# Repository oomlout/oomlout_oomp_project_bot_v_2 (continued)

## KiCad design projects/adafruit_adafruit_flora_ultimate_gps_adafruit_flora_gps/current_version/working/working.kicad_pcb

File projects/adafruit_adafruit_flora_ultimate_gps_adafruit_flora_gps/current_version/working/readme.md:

# adafruit_flora_ultimate_gps
 
## summary 
* id: adafruit_adafruit_flora_ultimate_gps_adafruit_flora_gps
* user: adafruit
* name: adafruit_flora_ultimate_gps
* board: adafruit_flora_gps
* repo: https://github.com/adafruit/Adafruit-Flora-Ultimate-GPS

* src_file_repo_sch: 
* src_file_repo_sch_link: https://github.com/adafruit/Adafruit-Flora-Ultimate-GPS/tree/master/
* full details link: https://github.com/oomlout/oomlout_oomp_project_bot_v_2/tree/main/projects/adafruit_adafruit_flora_ultimate_gps_adafruit_flora_gps/current_version/working  

## schematic  
  
[schematic (pdf)](working_schematic.pdf) 

## pcb  

[board (pdf)](working.pdf)  

## working_bom
| Id | Designator | Footprint | Quantity | Designation | Supplier and ref |  | None | 
| --- | --- | --- | --- | --- | --- | --- | --- | 
| 1 | FID2,FID1 | FIDUCIAL_1MM | 2 | FIDUCIAL" |  |  | [''] | 
| 2 | C2 | 0805 | 1 | 10uF |  |  | [''] | 
| 3 | TX0,TP4,UNK3V3IN0,GND0,RX0,TP1,GND1 | SEWINGTAP_2.0 | 7 | SEWTAP-2.0IN |  |  | [''] | 
| 4 | U$6 | ADAFRUIT_5MM | 1 |  |  |  | [''] | 
| 5 | R1 | 0805 | 1 | 1K |  |  | [''] | 
| 6 | LED1 | CHIPLED_0805 | 1 | FIX |  |  | [''] | 
| 7 | U1 | FGPMMOPA6H | 1 | FGPMMOPA6H |  |  | [''] | 
| 8 | FB1 | 0805 | 1 | Ferrite |  |  | [''] | 
| 9 | U$20 | U.FL | 1 | U.FL |  |  | [''] | 
| 10 | U$7 | FLORASMALL | 1 |  |  |  | [''] | 

## bom_schematic
| Ref | Qnty | Value | Cmp name | Footprint | Description | Vendor | DNP | 
| --- | --- | --- | --- | --- | --- | --- | --- | 
| C2 | 1 | 10uF | CAP_CERAMIC0805 | working:0805 |  |  |  | 
| FB1 | 1 | Ferrite | FERRITE0805 | working:0805 |  |  |  | 
| FID1, FID2 | 2 | FIDUCIAL"" | FIDUCIAL{dblquote}{dblquote} | working:FIDUCIAL_1MM |  |  |  | 
| GND0, GND1 | 2 | SEWTAP-2.0IN | SEWTAP-2.0IN | working:SEWINGTAP_2.0 |  |  |  | 
| LED1 | 1 | FIX | LED0805 | working:CHIPLED_0805 |  |  |  | 
| R1 | 1 | 1K | RESISTOR0805 | working:0805 |  |  |  | 
| RX0 | 1 | SEWTAP-2.0IN | SEWTAP-2.0IN | working:SEWINGTAP_2.0 |  |  |  | 
| TP1, TP4 | 2 | SEWTAP-2.0IN | SEWTAP-2.0IN | working:SEWINGTAP_2.0 |  |  |  | 
| TX0 | 1 | SEWTAP-2.0IN | SEWTAP-2.0IN | working:SEWINGTAP_2.0 |  |  |  | 
| U1 | 1 | FGPMMOPA6H | GPS_FGPMMOPA6H | working:FGPMMOPA6H |  |  |  | 
| U$20 | 1 | U.FL | U.FL | working:U.FL |  |  |  | 
| UNK3V3IN0 | 1 | SEWTAP-2.0IN | SEWTAP-2.0IN | working:SEWINGTAP_2.0 |  |  |  |

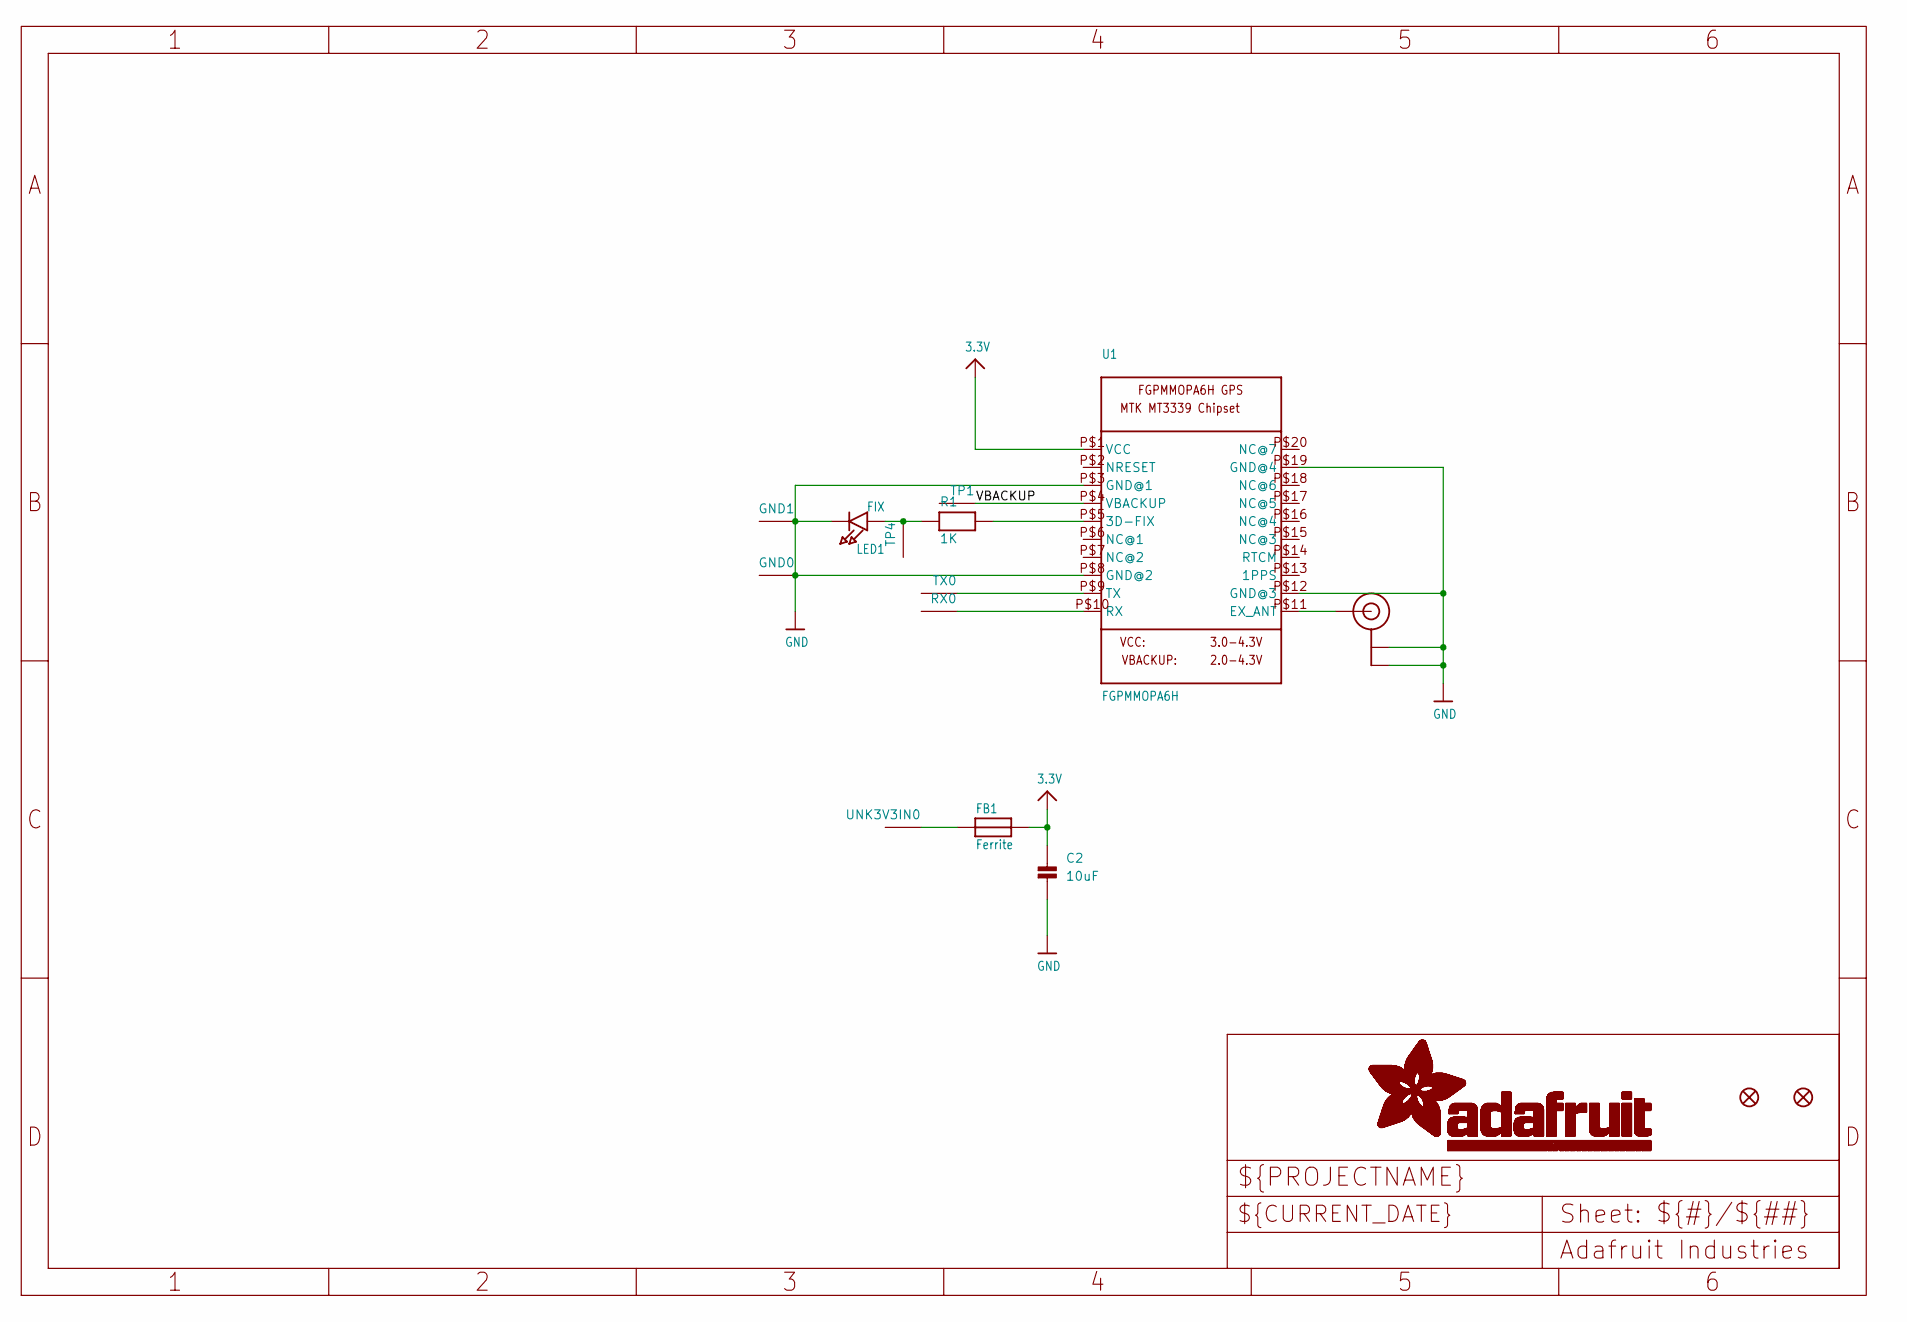
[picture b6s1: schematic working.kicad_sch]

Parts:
C2: 10uF; 0805
FB1: Ferrite; 0805
FID1, FID2: FIDUCIAL""; FIDUCIAL_1MM
GND0, GND1: SEWTAP-2.0IN; SEWINGTAP_2.0
LED1: FIX; CHIPLED_0805
R1: 1K; 0805
RX0: SEWTAP-2.0IN; SEWINGTAP_2.0
TP1, TP4: SEWTAP-2.0IN; SEWINGTAP_2.0
TX0: SEWTAP-2.0IN; SEWINGTAP_2.0
U1: FGPMMOPA6H
U$20: U.FL
UNK3V3IN0: SEWTAP-2.0IN; SEWINGTAP_2.0

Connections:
3.3V: C2.1, FB1.2, U1.P$1 (VCC)
GND: C2.2, GND0.P$1, GND1.P$1, LED1.C, U1.P$3 (GND@1), U1.P$8 (GND@2), U1.P$12 (GND@3), U1.P$19 (GND@4), U$20.P$1 (GND@0), U$20.P$2 (GND@1)
unnamed: LED1.A, R1.1, TP4.P$1
unnamed: R1.2, U1.P$5 (3D-FIX)
unnamed: FB1.1, UNK3V3IN0.P$1
unnamed: U1.P$11 (EX_ANT), U$20.P$3 (SIGNAL)
RX: RX0.P$1, U1.P$10 (RX)
TX: TX0.P$1, U1.P$9 (TX)
VBACKUP: TP1.P$1, U1.P$4 (VBACKUP)

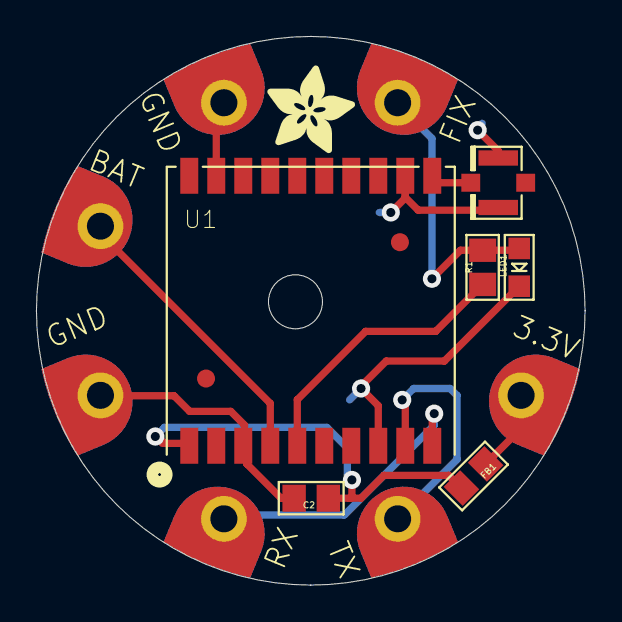
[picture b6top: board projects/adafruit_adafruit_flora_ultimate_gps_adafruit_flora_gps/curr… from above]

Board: 2 copper layers, 30.5 x 30.5 mm, 17 parts (1 on the bottom side), 9 nets.

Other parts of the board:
U$6: ADAFRUIT_5MM
U$7: FLORASMALL

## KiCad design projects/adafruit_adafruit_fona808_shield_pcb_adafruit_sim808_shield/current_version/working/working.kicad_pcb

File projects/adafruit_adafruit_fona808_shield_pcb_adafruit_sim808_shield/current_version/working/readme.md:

# adafruit_fona808_shield_pcb
 
## summary 
* id: adafruit_adafruit_fona808_shield_pcb_adafruit_sim808_shield
* user: adafruit
* name: adafruit_fona808_shield_pcb
* board: adafruit_sim808_shield
* repo: https://github.com/adafruit/Adafruit-FONA808-Shield-PCB

* src_file_repo_sch: 
* src_file_repo_sch_link: https://github.com/adafruit/Adafruit-FONA808-Shield-PCB/tree/master/
* full details link: https://github.com/oomlout/oomlout_oomp_project_bot_v_2/tree/main/projects/adafruit_adafruit_fona808_shield_pcb_adafruit_sim808_shield/current_version/working  

## schematic  
  
[schematic (pdf)](working_schematic.pdf) 

## pcb  

[board (pdf)](working.pdf)  

## working_bom
| Id | Designator | Footprint | Quantity | Designation | Supplier and ref |  | None | 
| --- | --- | --- | --- | --- | --- | --- | --- | 
| 1 | D4,D7,D3,D6,D9,D5 | SOD-323 | 6 | 1N4148 |  |  | [''] | 
| 2 | M1 | ARDUINOR3_ICSP_NODIM | 1 | ARDUINO_R3_ICSP_NODIM |  |  | [''] | 
| 3 | X3 | U.FL | 1 | uFL |  |  | [''] | 
| 4 | PWRSTAT0,DONE0 | CHIPLED_0805_NOOUTLINE | 2 | GREEN |  |  | [''] | 
| 5 | JP6,JP5 | 1X08_ROUND_76 | 2 |  |  |  | [''] | 
| 6 | U$64 | PCBFEAT-REV-040 | 1 |  |  |  | [''] | 
| 7 | U2 | SOT23-5 | 1 | MCP73831T-2ACI/OT |  |  | [''] | 
| 8 | R4,R5,R2 | 0805-NO | 3 | 1K |  |  | [''] | 
| 9 | C9,C11 | 0805-NO | 2 | 10uF |  |  | [''] | 
| 10 | U$41,U$33,U$34 | SYMBOL_MINUS | 3 |  |  |  | [''] | 
| 11 | R3 | 0805-NO | 1 | 2K |  |  | [''] | 
| 12 | U$35,U$20,U$2 | SYMBOL_PLUS | 3 |  |  |  | [''] | 
| 13 | X6 | C707_10M006_512_2 | 1 | SIM_LOCKAMPHENOL |  |  | [''] | 
| 14 | JP10 | 1X08_ROUND_70 | 1 |  |  |  | [''] | 
| 15 | C6,C2 | 0805-NO | 2 | 33pF |  |  | [''] | 
| 16 | SJ1 | SOLDERJUMPER_2WAY_OPEN_NOPASTE | 1 |  |  |  | [''] | 
| 17 | SW2 | EG1390 | 1 | EG1390 |  |  | [''] | 
| 18 | @HOLE3,@HOLE0,@HOLE2,@HOLE1 |  | 4 |  |  |  | [''] | 
| 19 | SW1 | EVQ-Q2 | 1 | EVQQ2 |  |  | [''] | 
| 20 | CN2 | JSTPH2 | 1 | JSTPH |  |  | [''] | 
| 21 | FID1,FID3,FID2 | FIDUCIAL_1MM | 3 | FIDUCIAL" |  |  | [''] | 
| 22 | JP4 | 1X10_ROUND70 | 1 |  |  |  | [''] | 
| 23 | U3 | SIM900_SMT | 1 | SIM808 |  |  | [''] | 
| 24 | C14,C16 | RESPACK_4X0603 | 2 | 33pF |  |  | [''] | 
| 25 | U$36 | ADAFRUIT_5MM | 1 |  |  |  | [''] | 
| 26 | SJ7 | SOLDERJUMPER_ARROW_NOPASTE | 1 |  |  |  | [''] | 
| 27 | D1 | SOD-123 | 1 | MMSZ5231BT1G |  |  | [''] | 
| 28 | JP1,JP2 | 1X02_ROUND | 2 |  |  |  | [''] | 
| 29 | SJ6,SJ2,SJ5,SJ3,SJ4 | SOLDERJUMPER_CLOSEDWIRE | 5 |  |  |  | [''] | 
| 30 | C1 | 0805-NO | 1 | 10ÂµF |  |  | [''] | 
| 31 | D8 | SOD-123 | 1 | MBR120 |  |  | [''] | 
| 32 | JP3 | 1X02_ROUND | 1 | BUZZ |  |  | [''] | 
| 33 | C15,C17 | RESPACK_4X0603 | 2 | 10pF |  |  | [''] | 
| 34 | L2 | _0805MP | 1 | 33nH |  |  | [''] | 
| 35 | Q1 | SC59-BEC | 1 | DTC143ZUAT106 |  |  | [''] | 
| 36 | D2 | SOT363 | 1 | SMF05C |  |  | [''] | 
| 37 | PPS0,PWM0,DTR0 | 1X01-CLEANBIG | 3 |  |  |  | [''] | 
| 38 | CHRG0 | CHIPLED_0805_NOOUTLINE | 1 | ORANGE |  |  | [''] | 
| 39 | NETSTAT0 | CHIPLED_0805_NOOUTLINE | 1 | BLUE |  |  | [''] | 
| 40 | R6 | 0805-NO | 1 | 10K |  |  | [''] | 
| 41 | R1 | 0805-NO | 1 | 470 |  |  | [''] | 
| 42 | X1 | SMA_EDGELAUNCH_UFL | 1 | uFL |  |  | [''] | 
| 43 | C7 | C1210 | 1 | 100uF |  |  | [''] | 
| 44 | X4 | 4UCONN_18510 | 1 | 4UCONN_18510 |  |  | [''] | 
| 45 | IC1 | TSSOP14 | 1 | 74VHCT125PW |  |  | [''] | 
| 46 | C5 | 0805-NO | 1 | 10pF |  |  | [''] | 
| 47 | JP7 | 1X06_ROUND_76 | 1 |  |  |  | [''] | 
| 48 | TP1 | TP11R | 1 | TPTP11R |  |  | [''] | 
| 49 | U$25 | ADAFRUIT_TEXT_30MM | 1 |  |  |  | [''] | 
| 50 | U$26 | FONA_LOGO | 1 |  |  |  | [''] | 

## bom_schematic
| Ref | Qnty | Value | Cmp name | Footprint | Description | Vendor | DNP | 
| --- | --- | --- | --- | --- | --- | --- | --- | 
| C1 | 1 | 10ÂµF | CAP_CERAMIC0805-NOOUTLINE | working:0805-NO |  |  |  | 
| C2, C6 | 2 | 33pF | CAP_CERAMIC0805-NOOUTLINE | working:0805-NO |  |  |  | 
| C5 | 1 | 10pF | CAP_CERAMIC0805-NOOUTLINE | working:0805-NO |  |  |  | 
| C7 | 1 | 100uF | C-USC1210 | working:C1210 |  |  |  | 
| C9, C11 | 2 | 10uF | CAP_CERAMIC0805-NOOUTLINE | working:0805-NO |  |  |  | 
| C14, C16 | 2 | 33pF | CAP_4PACK1206 | working:RESPACK_4X0603 |  |  |  | 
| C15, C17 | 2 | 10pF | CAP_4PACK1206 | working:RESPACK_4X0603 |  |  |  | 
| CHRG0 | 1 | ORANGE | LED0805_NOOUTLINE | working:CHIPLED_0805_NOOUTLINE |  |  |  | 
| CN2 | 1 | JSTPH | JST_2PIN | working:JSTPH2 |  |  |  | 
| D1 | 1 | MMSZ5231BT1G | DIODE-ZENERSOD123 | working:SOD-123 |  |  |  | 
| D2 | 1 | SMF05C | TVSARRAY_5LANE | working:SOT363 |  |  |  | 
| D3, D4, D5, D6, D7, D9 | 6 | 1N4148 | DIODESOD-323 | working:SOD-323 |  |  |  | 
| D8 | 1 | MBR120 | DIODE-SCHOTTKYSOD-123 | working:SOD-123 |  |  |  | 
| DONE0 | 1 | GREEN | LED0805_NOOUTLINE | working:CHIPLED_0805_NOOUTLINE |  |  |  | 
| DTR0 | 1 | PINHD-1X1CB | PINHD-1X1CB | working:1X01-CLEANBIG |  |  |  | 
| FID1, FID2, FID3 | 3 | FIDUCIAL"" | FIDUCIAL{dblquote}{dblquote} | working:FIDUCIAL_1MM |  |  |  | 
| IC1 | 1 | 74125PW | 74125PW | working:TSSOP14 |  |  |  | 
| JP1, JP2 | 2 | HEADER-1X2ROUND | HEADER-1X2ROUND | working:1X02_ROUND |  |  |  | 
| JP3 | 1 | BUZZ | HEADER-1X2ROUND | working:1X02_ROUND |  |  |  | 
| JP4 | 1 | HEADER-1X1070MIL | HEADER-1X1070MIL | working:1X10_ROUND70 |  |  |  | 
| JP5, JP6 | 2 | HEADER-1X876MIL | HEADER-1X876MIL | working:1X08_ROUND_76 |  |  |  | 
| JP7 | 1 | HEADER-1X676MIL | HEADER-1X676MIL | working:1X06_ROUND_76 |  |  |  | 
| JP10 | 1 | HEADER-1X870MIL | HEADER-1X870MIL | working:1X08_ROUND_70 |  |  |  | 
| L2 | 1 | 33nH | INDUCTOR_0805MP | working:_0805MP |  |  |  | 
| M1 | 1 | ARDUINO_R3_ICSP_NODIM | ARDUINO_R3_ICSP_NODIM | working:ARDUINOR3_ICSP_NODIM |  |  |  | 
| NETSTAT0 | 1 | BLUE | LED0805_NOOUTLINE | working:CHIPLED_0805_NOOUTLINE |  |  |  | 
| PPS0 | 1 | PINHD-1X1CB | PINHD-1X1CB | working:1X01-CLEANBIG |  |  |  | 
| PWM0 | 1 | PINHD-1X1CB | PINHD-1X1CB | working:1X01-CLEANBIG |  |  |  | 
| PWRSTAT0 | 1 | GREEN | LED0805_NOOUTLINE | working:CHIPLED_0805_NOOUTLINE |  |  |  | 
| Q1 | 1 | DTC143ZUAT106 | -NPN_DRIVER-SC59-BEC | working:SC59-BEC |  |  |  | 
| R1 | 1 | 470 | RESISTOR0805_NOOUTLINE | working:0805-NO |  |  |  | 
| R2, R4, R5 | 3 | 1K | RESISTOR0805_NOOUTLINE | working:0805-NO |  |  |  | 
| R3 | 1 | 2K | RESISTOR0805_NOOUTLINE | working:0805-NO |  |  |  | 
| R6 | 1 | 10K | RESISTOR0805_NOOUTLINE | working:0805-NO |  |  |  | 
| SJ1 | 1 | SOLDERJUMPER_2WAY | SOLDERJUMPER_2WAY | working:SOLDERJUMPER_2WAY_OPEN_NOPASTE |  |  |  | 
| SJ2, SJ3, SJ4, SJ5, SJ6 | 5 | SOLDERJUMPER_CLOSED | SOLDERJUMPER_CLOSED | working:SOLDERJUMPER_CLOSEDWIRE |  |  |  | 
| SJ7 | 1 | SOLDERJUMPER | SOLDERJUMPER | working:SOLDERJUMPER_ARROW_NOPASTE |  |  |  | 
| SW1 | 1 | EVQQ2 | SWITCH_TACT_SMT | working:EVQ-Q2 |  |  |  | 
| SW2 | 1 | EG1390 | SWITCH_DPDTEG1390 | working:EG1390 |  |  |  | 
| TP1 | 1 | TPTP11R | TPTP11R | working:TP11R |  |  |  | 
| U2 | 1 | MCP73831T-2ACI/OT | MCP73831/2 | working:SOT23-5 |  |  |  | 
| U3 | 1 | SIM808 | GSM_SIM808_LITERAL | working:SIM900_SMT |  |  |  | 
| X1 | 1 | uFL | SMACONNECTOR_EDGE_UFL | working:SMA_EDGELAUNCH_UFL |  |  |  | 
| X3 | 1 | uFL | ANTENNA_U.FL | working:U.FL |  |  |  | 
| X4 | 1 | 4UCONN_18510 | AUDIO_3.5MMJACK_4POL | working:4UCONN_18510 |  |  |  | 
| X6 | 1 | SIM_LOCKAMPHENOL | SIM_LOCKAMPHENOL | working:C707_10M006_512_2 |  |  |  |

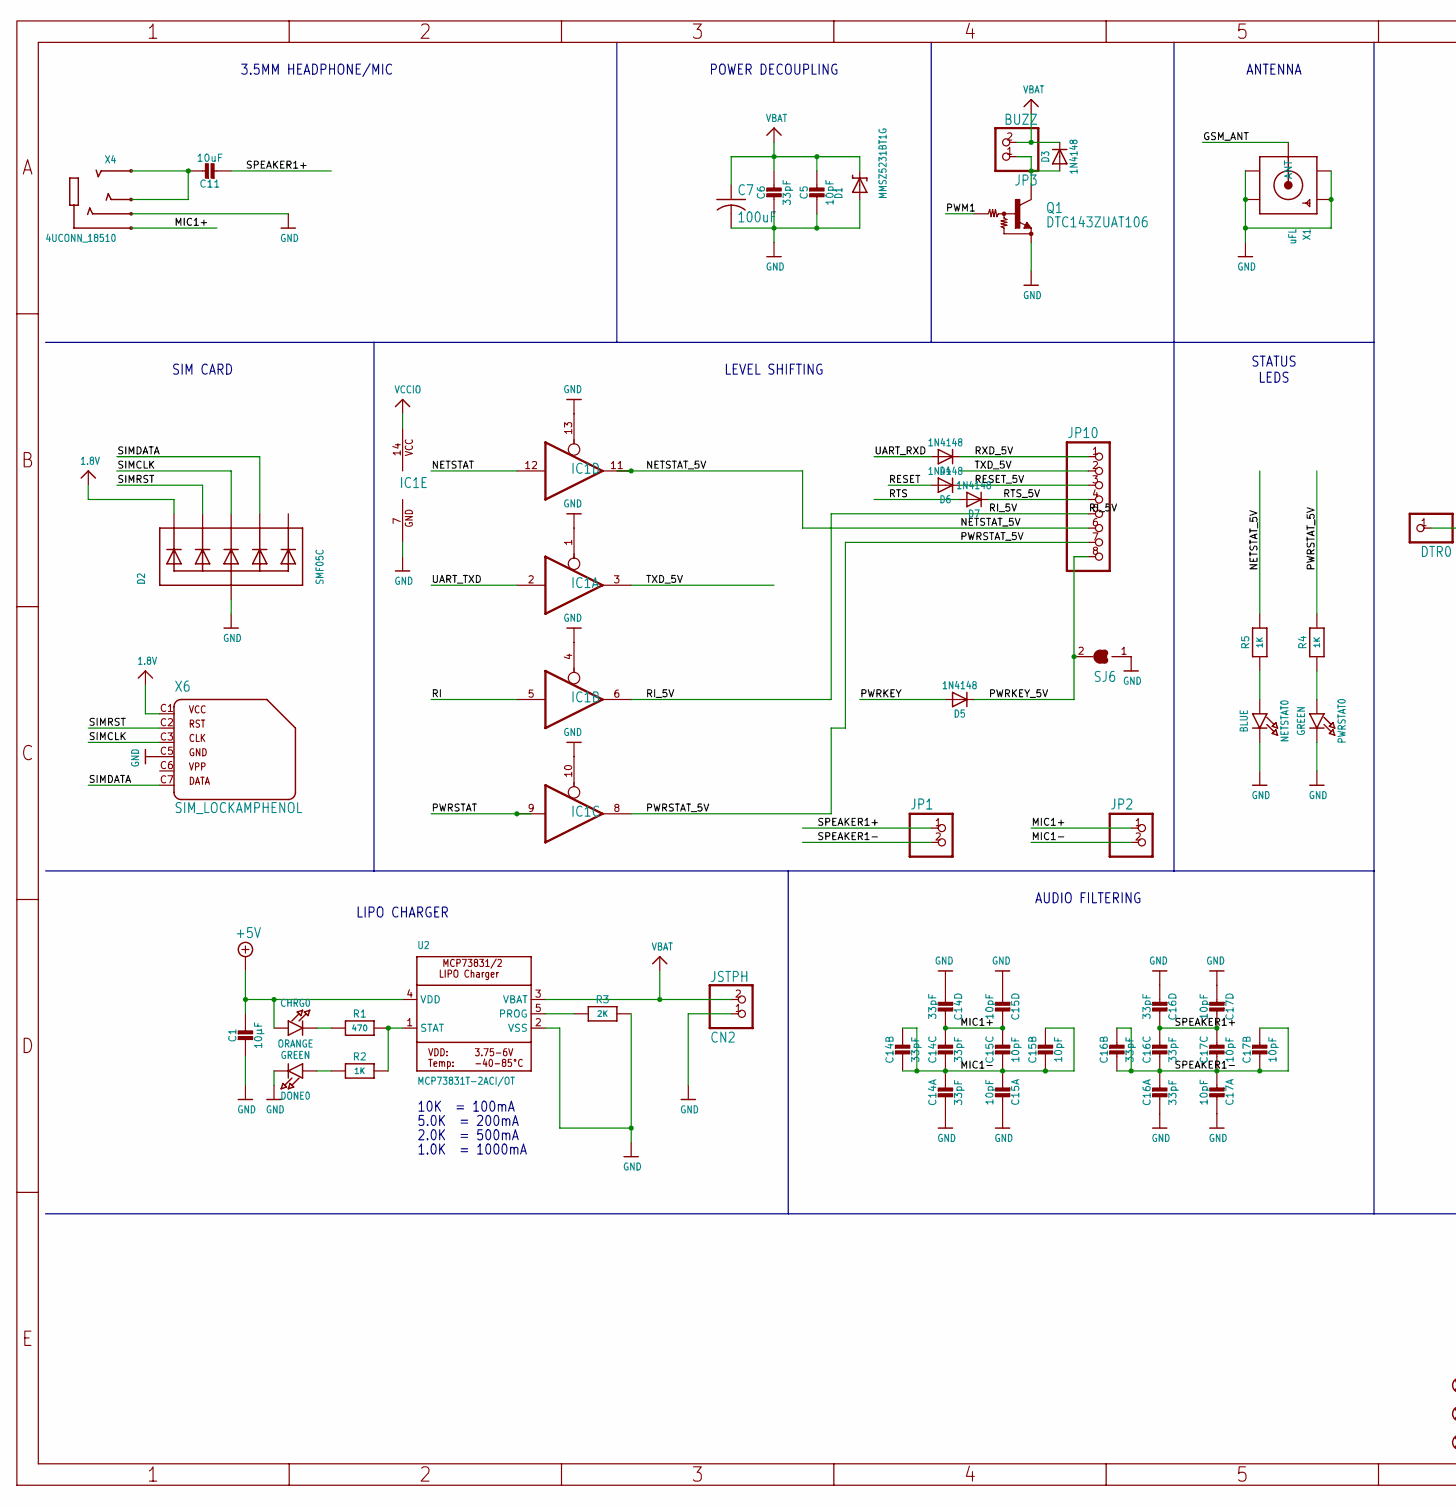
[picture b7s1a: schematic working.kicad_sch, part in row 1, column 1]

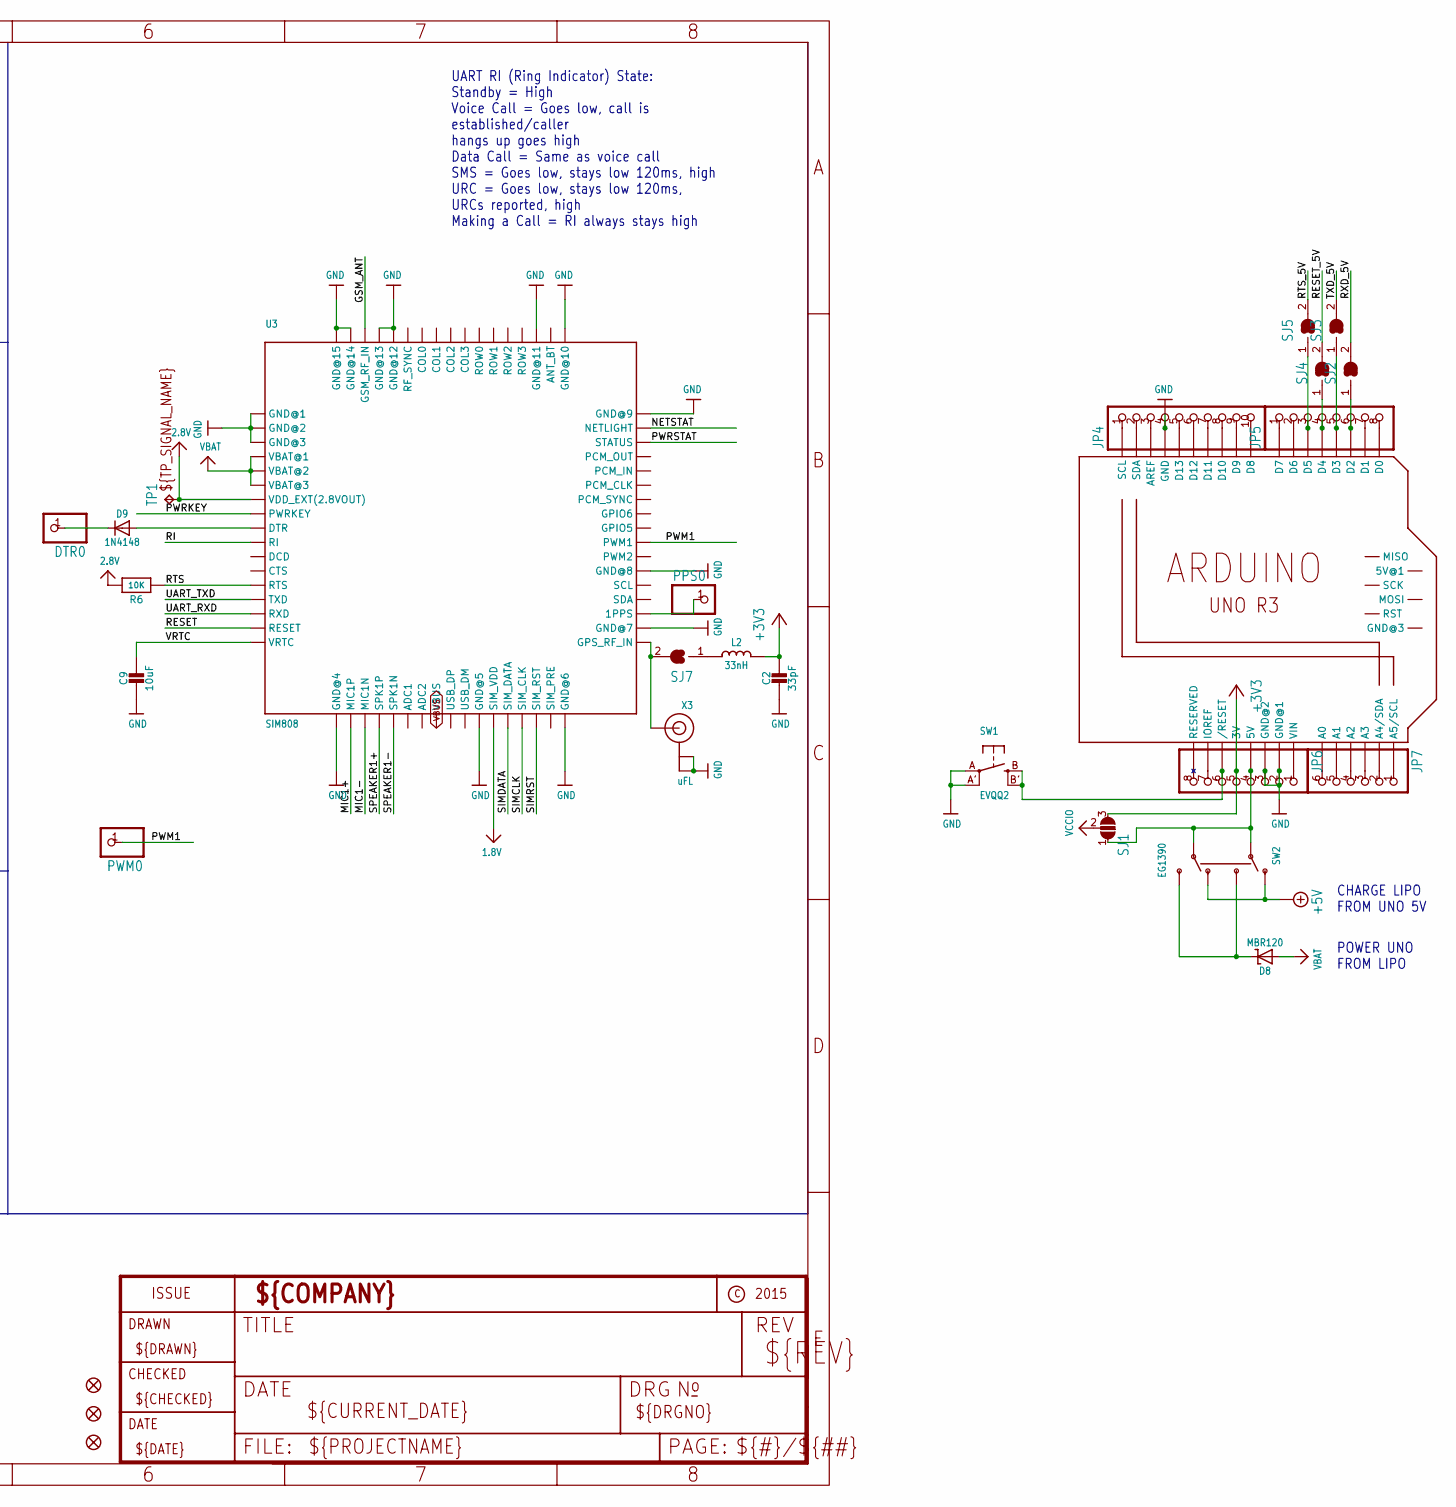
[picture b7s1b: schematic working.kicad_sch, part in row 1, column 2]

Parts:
C1: 10µF; 0805-NO
C2, C6: 33pF; 0805-NO
C5: 10pF; 0805-NO
C7: 100uF; C1210
C9, C11: 10uF; 0805-NO
C14, C16: 33pF; RESPACK_4X0603
C15, C17: 10pF; RESPACK_4X0603
CHRG0: ORANGE; CHIPLED_0805_NOOUTLINE
CN2: JSTPH; JSTPH2
D1: MMSZ5231BT1G; SOD-123
D2: SMF05C; SOT363
D3, D4, D5, D6, D7, D9: 1N4148; SOD-323
D8: MBR120; SOD-123
DONE0: GREEN; CHIPLED_0805_NOOUTLINE
DTR0: PINHD-1X1CB; 1X01-CLEANBIG
FID1, FID2, FID3: FIDUCIAL""; FIDUCIAL_1MM
IC1: 74125PW; TSSOP14
JP1, JP2: HEADER-1X2ROUND; 1X02_ROUND
JP3: BUZZ; 1X02_ROUND
JP4: HEADER-1X1070MIL; 1X10_ROUND70
JP5, JP6: HEADER-1X876MIL; 1X08_ROUND_76
JP7: HEADER-1X676MIL; 1X06_ROUND_76
JP10: HEADER-1X870MIL; 1X08_ROUND_70
L2: 33nH; _0805MP
M1: ARDUINO_R3_ICSP_NODIM; ARDUINOR3_ICSP_NODIM
NETSTAT0: BLUE; CHIPLED_0805_NOOUTLINE
PPS0: PINHD-1X1CB; 1X01-CLEANBIG
PWM0: PINHD-1X1CB; 1X01-CLEANBIG
PWRSTAT0: GREEN; CHIPLED_0805_NOOUTLINE
Q1: DTC143ZUAT106; SC59-BEC
R1: 470; 0805-NO
R2, R4, R5: 1K; 0805-NO
R3: 2K; 0805-NO
R6: 10K; 0805-NO
SJ1: SOLDERJUMPER_2WAY; SOLDERJUMPER_2WAY_OPEN_NOPASTE
SJ2, SJ3, SJ4, SJ5, SJ6: SOLDERJUMPER_CLOSED; SOLDERJUMPER_CLOSEDWIRE
SJ7: SOLDERJUMPER; SOLDERJUMPER_ARROW_NOPASTE
SW1: EVQQ2; EVQ-Q2
SW2: EG1390
TP1: TPTP11R; TP11R
U2: MCP73831T-2ACI/OT; SOT23-5
U3: SIM808; SIM900_SMT
X1: uFL; SMA_EDGELAUNCH_UFL
X3: uFL; U.FL
X4: 4UCONN_18510
X6: SIM_LOCKAMPHENOL; C707_10M006_512_2

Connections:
1.8V: D2.1 (C1), U3.P$29 (SIM_VDD), X6.C1 (1)
2.8V: R6.2, TP1.TP, U3.P$7 (VDD_EXT(2.8VOUT))
5V: JP6.4, M1.5V, SJ1.1, SW2.P1, SW2.P2
+3V3: C2.1, JP6.5, L2.2, M1.3V, SJ1.3
+5V: C1.1, CHRG0.A, SW2.O1, SW2.O2, U2.4 (VDD)
A0: JP7.6, M1.A0
A1: JP7.5, M1.A1
A2: JP7.4, M1.A2
A3: JP7.3, M1.A3
A4: JP7.2, M1.A4 (A4/SDA)
A5: JP7.1, M1.A5 (A5/SCL)
AREF: JP4.3, M1.AREF
BUZZ-: D3.A, JP3.1, Q1.C
D0: JP5.8, M1.D0
D1: JP5.7, M1.D1
D2: JP5.6, M1.D2, SJ2.1
D3: JP5.5, M1.D3, SJ3.1
D4: JP5.4, M1.D4, SJ4.1
D5: JP5.3, M1.D5, SJ5.1
D6: JP5.2, M1.D6
D7: JP5.1, M1.D7
D8: JP4.10, M1.D8
D9: JP4.9, M1.D9
D10: JP4.8, M1.D10
D11: JP4.7, M1.D11
D12: JP4.6, M1.D12
D13: JP4.5, M1.D13
DTR_5V: D9.C, DTR0.1
GND: C1.2, C2.2, C5.2, C6.2, C7.2, C9.2, C14.5 (2), C14.8 (2), C15.4 (1), C15.8 (2), C16.5 (2), C16.8 (2), C17.4 (1), C17.8 (2), CN2.1, D1.A, D2.2 (A), DONE0.C, IC1.1 (OE), IC1.4 (OE), IC1.7 (GND), IC1.10 (OE), IC1.13 (OE), JP4.4, JP6.2, JP6.3, M1.GND, M1.GND@1 (GND@2), M1.GND@3 (GND@1), NETSTAT0.C, PWRSTAT0.C, Q1.E, R3.2, SJ6.1, SW1.A, SW1.A' (P1), U2.2 (VSS), U3.P$1 (GND@1), U3.P$2 (GND@2), U3.P$3 (GND@3), U3.P$18 (GND@4), U3.P$28 (GND@5), U3.P$34 (GND@6), U3.P$36 (GND@7), U3.P$40 (GND@8), U3.P$51 (GND@9), U3.P$52 (GND@10), U3.P$54 (GND@11), U3.P$64 (GND@12), U3.P$65 (GND@13), U3.P$67 (GND@14), U3.P$68 (GND@15), X1.GND@1 (GND1), X1.GND@2 (GND2), X1.GND@3 (GND3), X1.GND@4 (GND4), X3.1 (GND@0), X3.2 (GND@1), X4.4-INNER_SLEEVE (RING1), X6.C5 (4)
GPS_PPS: PPS0.1, U3.P$37 (1PPS)
GSM_ANT: U3.P$66 (GSM_RF_IN), X1.P (ANT)
HP+: C11.1, X4.2-TIP (RING3), X4.3-OUTER_SLEEVE (RING2)
IOREF: JP6.7, M1.IOREF
MIC1+: C14.1, C14.2 (1), C15.1, C15.2 (1), JP2.1, U3.P$19 (MIC1P), X4.1-GND (TIP)
MIC1-: C14.3 (1), C14.4 (1), C14.6 (2), C14.7 (2), C15.3 (1), C15.5 (2), C15.6 (2), C15.7 (2), JP2.2, U3.P$20 (MIC1N)
unnamed: CHRG0.C, R1.1
unnamed: R1.2, R2.2, U2.1 (STAT)
unnamed: SJ7.2, U3.P$35 (GPS_RF_IN), X3.3 (SIGNAL)
unnamed: PWRSTAT0.A, R4.1
unnamed: R3.1, U2.5 (PROG)
unnamed: DONE0.A, R2.1
unnamed: NETSTAT0.A, R5.1
unnamed: D8.C, SW2.S1, SW2.S2
unnamed: L2.1, SJ7.1
unnamed: D9.A, U3.P$9 (DTR)
NC: JP6.8, M1.RESERVED
NETSTAT: IC1.12 (I), U3.P$50 (NETLIGHT)
NETSTAT_5V: IC1.11 (O), JP10.6, R5.2
PWM1: PWM0.1, Q1.B, U3.P$42 (PWM1)
PWRKEY: D5.A, U3.P$8 (PWRKEY)
PWRKEY_5V: D5.C, JP10.8, SJ6.2
PWRSTAT: IC1.9 (I), U3.P$49 (STATUS)
PWRSTAT_5V: IC1.8 (O), JP10.7, R4.2
RESET: D6.A, U3.P$16 (RESET)
RESET_5V: D6.C, JP10.3, SJ4.2
RI: IC1.5 (I), U3.P$10 (RI)
RI_5V: IC1.6 (O), JP10.5
RST: JP6.6, M1.RESET (/RESET), SW1.B (S), SW1.B' (S1)
RTS: D7.A, R6.1, U3.P$13 (RTS)
RTS_5V: D7.C, JP10.4, SJ5.2
RXD_5V: D4.C, JP10.1, SJ2.2
SCL: JP4.1, M1.SCL
SDA: JP4.2, M1.SDA
SIMCLK: D2.4 (C3), U3.P$31 (SIM_CLK), X6.C3 (3)
SIMDATA: D2.5 (C4), U3.P$30 (SIM_DATA), X6.C7 (6)
SIMRST: D2.3 (C2), U3.P$32 (SIM_RST), X6.C2 (2)
SPEAKER1+: C11.2, C16.1, C16.2 (1), C17.1, C17.2 (1), JP1.1, U3.P$21 (SPK1P)
SPEAKER1-: C16.3 (1), C16.4 (1), C16.6 (2), C16.7 (2), C17.3 (1), C17.5 (2), C17.6 (2), C17.7 (2), JP1.2, U3.P$22 (SPK1N)
TXD_5V: IC1.3 (O), JP10.2, SJ3.2
UART_RXD: D4.A, U3.P$15 (RXD)
UART_TXD: IC1.2 (I), U3.P$14 (TXD)
VBAT: C5.1, C6.1, C7.1, CN2.2, D1.C, D3.C, D8.A, JP3.2, U2.3 (VBAT), U3.P$4 (VBAT@1), U3.P$5 (VBAT@2), U3.P$6 (VBAT@3)
VBUS: U3.P$25 (VBUS)
VCCIO: IC1.14 (VCC), SJ1.2
VIN: JP6.1, M1.VIN
VRTC: C9.1, U3.P$17 (VRTC)

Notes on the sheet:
10K = 100mA
POWER DECOUPLING
UART RI (Ring Indicator) State: Standby = High Voice Call = Goes low, call is established/caller hangs up goes high Data Call = Same as voice call SMS = Goes low, stays low 120ms, high URC = Goes low, stays low 120ms, URCs reported, high Making a Call = RI always stays high
1.0K = 1000mA
ANTENNA
5.0K = 200mA
3.5MM HEADPHONE/MIC
CHARGE LIPO FROM UNO 5V
POWER UNO FROM LIPO
LIPO CHARGER
SIM CARD
LEVEL SHIFTING
AUDIO FILTERING
2.0K = 500mA
STATUS LEDS

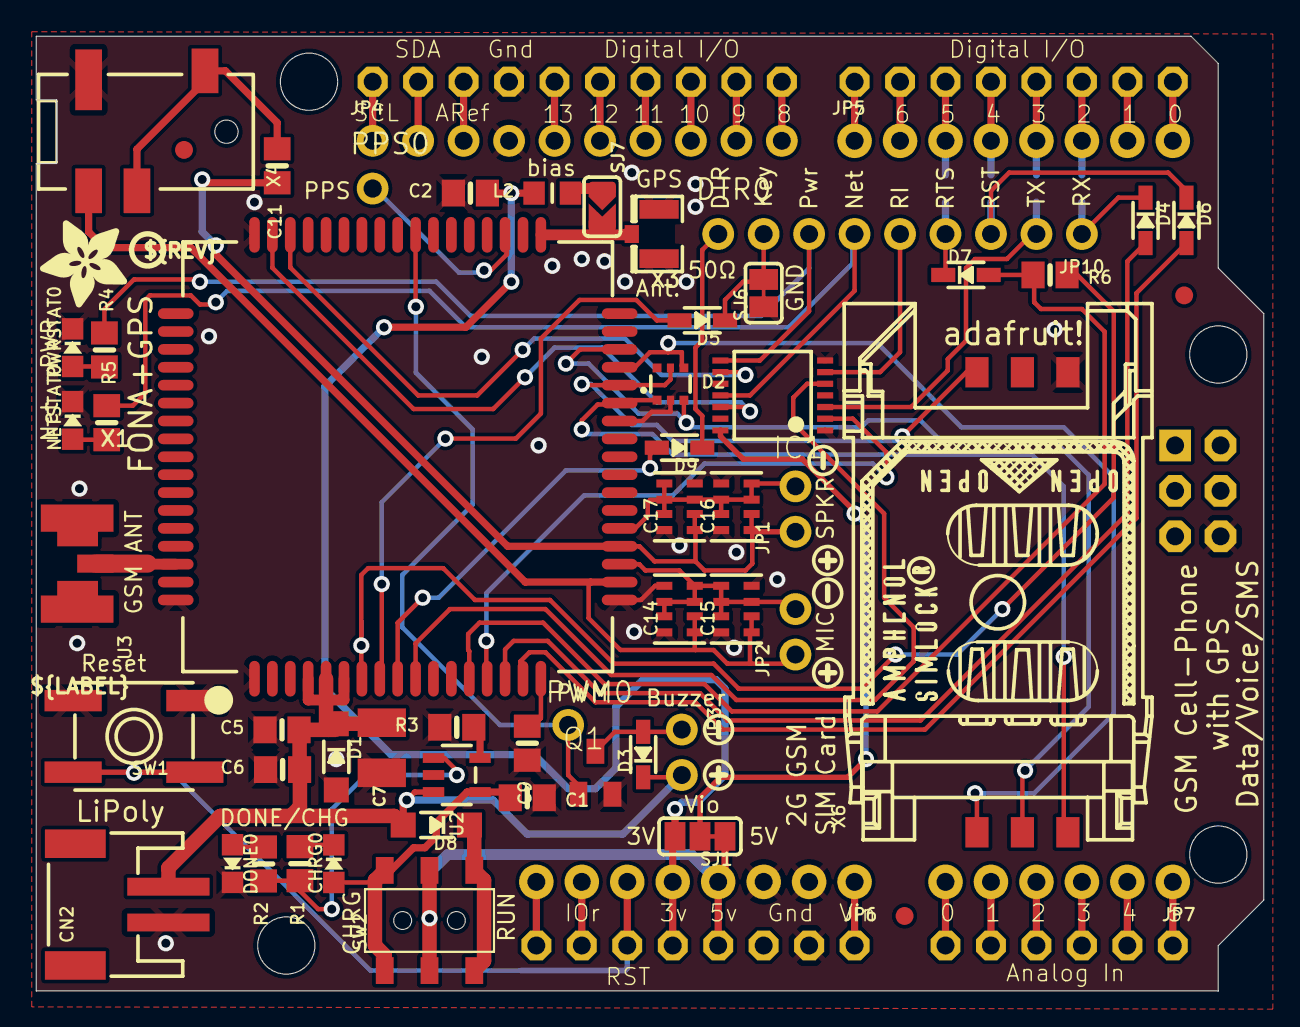
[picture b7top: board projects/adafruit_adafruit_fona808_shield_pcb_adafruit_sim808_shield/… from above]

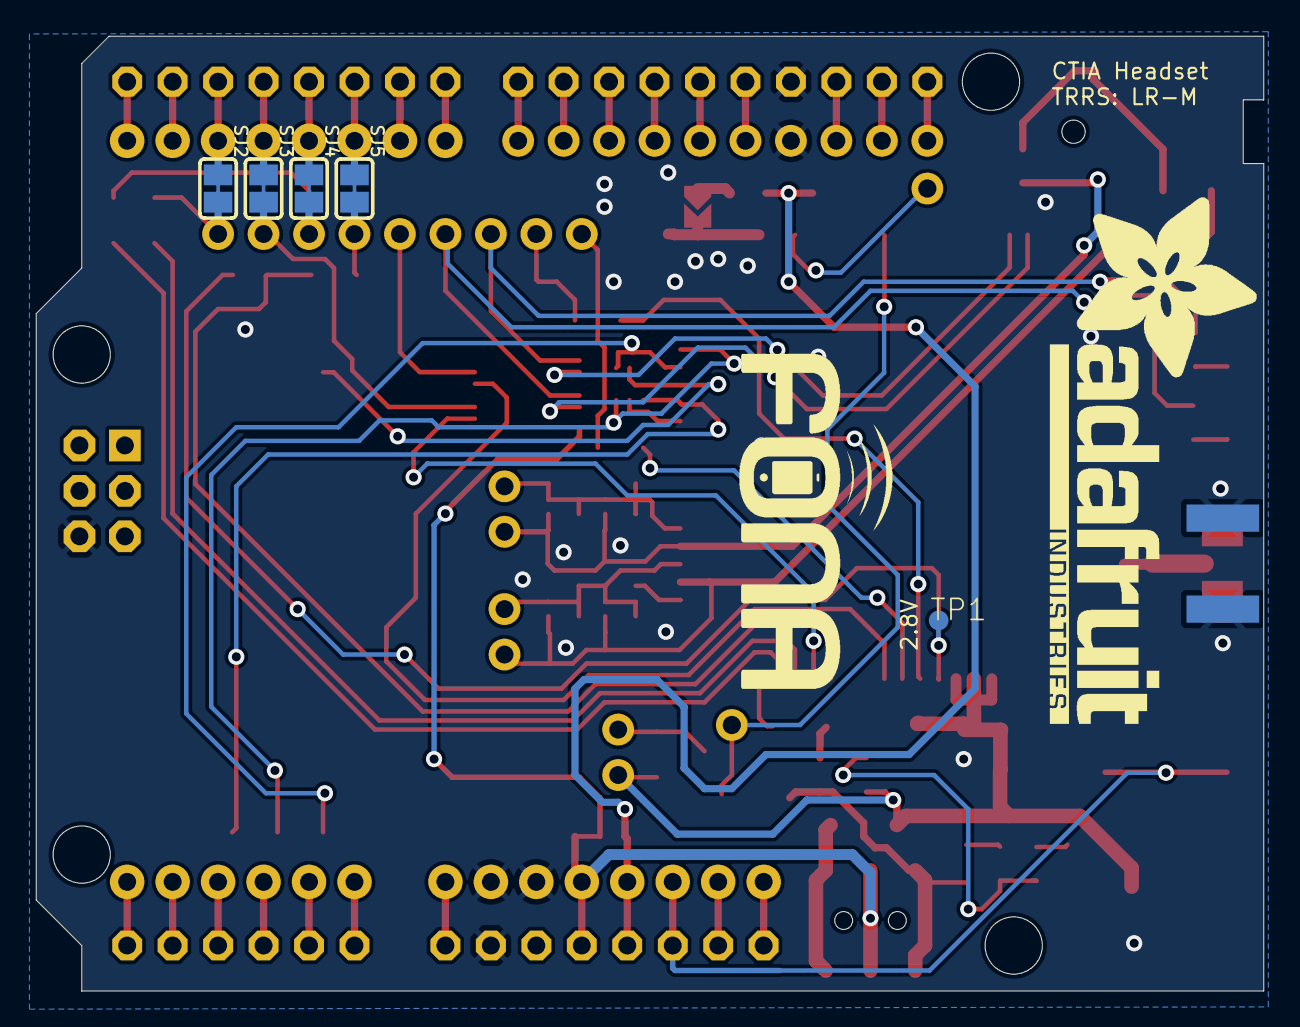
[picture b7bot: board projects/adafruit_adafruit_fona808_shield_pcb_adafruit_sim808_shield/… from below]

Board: 2 copper layers, 68.6 x 53.3 mm, 79 parts (7 on the bottom side), 75 nets.

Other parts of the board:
@HOLE0, @HOLE1, @HOLE2, @HOLE3: (no value)
U$2, U$20, U$35: SYMBOL_PLUS
U$25: ADAFRUIT_TEXT_30MM
U$26: FONA_LOGO
U$33, U$34, U$41: SYMBOL_MINUS
U$36: ADAFRUIT_5MM
U$64: PCBFEAT-REV-040
